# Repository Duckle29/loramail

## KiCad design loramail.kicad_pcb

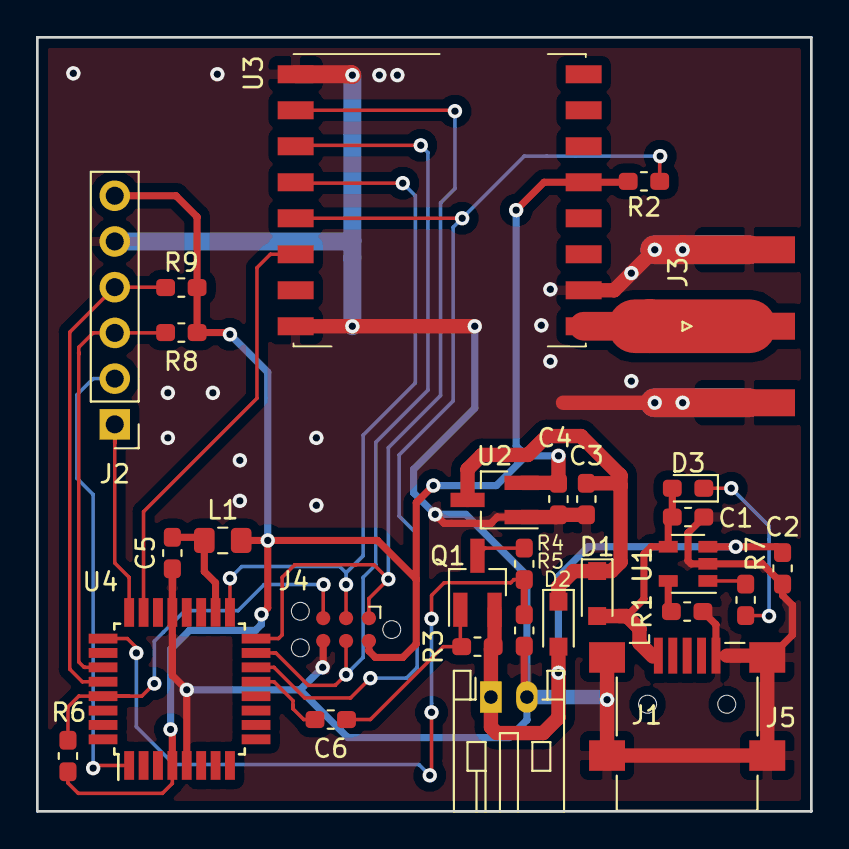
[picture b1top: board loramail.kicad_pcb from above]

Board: 2 copper layers, 43.0 x 43.0 mm, 29 parts (0 on the bottom side), 24 nets.

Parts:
C1, C2: 4.7uF; C_0603_1608Metric_Pad1.05x0.95mm_HandSolder
C3, C4: 1uF; C_0603_1608Metric_Pad1.05x0.95mm_HandSolder
C5, C6: 100nF; C_0603_1608Metric_Pad1.05x0.95mm_HandSolder
D1, D2: BAT54WS; D_SOD-323_HandSoldering
D3: red; LED_0603_1608Metric_Pad1.05x0.95mm_HandSolder
J1: lipo-cell; JST_PH_S2B-PH-K_1x02_P2.00mm_Horizontal
J2: VL53L0X; PinHeader_1x06_P2.54mm_Vertical
J3: SMA; SMA_Amphenol_132289_EdgeMount
J4: TC2030-ISP; Tag-Connect_TC2030-IDC-NL_2x03_P1.27mm_Vertical
J5: USB_B_Mini; USB_Mini-B_Lumberg_2486_01_Horizontal
L1: 10uH; L_0805_2012Metric_Pad1.15x1.40mm_HandSolder
Q1: SI2333; SOT-23_Handsoldering
R1, R7: 2k2; R_0603_1608Metric_Pad1.05x0.95mm_HandSolder
R2: 100k; R_0603_1608Metric_Pad1.05x0.95mm_HandSolder
R3, R6, R8, R9: 10k; R_0603_1608Metric_Pad1.05x0.95mm_HandSolder
R4: 1k2; R_0603_1608Metric_Pad1.05x0.95mm_HandSolder
R5: 3k3; R_0603_1608Metric_Pad1.05x0.95mm_HandSolder
U1: MCP73831-2-OT; SOT-23-5
U2: MCP1703A-3302_SOT23; SOT-23_Handsoldering
U3: RFM96W-433S2; HOPERF_RFM9XW_SMD
U4: ATmega328PB-AU; TQFP-32_7x7mm_P0.8mm

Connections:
+3V3: C4.1, J2.6, J4.2, L1.1, R2.2, R6.1, R8.1, R9.1, U2.2, U3.13, U4.4
+BATT: C2.1, D2.2, J1.1, Q1.2, R3.1, U1.3
/bat-sense: R4.2, R5.1, U4.25
/sample-bat: C6.1, U4.13
GND: C1.1, C2.2, C3.2, C4.2, C5.2, J1.2, J2.5, J3.2, J4.6, J5.5, J5.6, R1.1, R5.2, U1.2, U2.1, U3.1, U3.8, U3.10, U4.5, U4.21
MISO: J4.1, U3.2, U4.16
MOSI: J4.4, U3.3, U4.15
NSS: R2.1, U3.5, U4.14
unnamed: C3.1, D1.1, D2.1, U2.3
unnamed: C5.1, L1.2, U4.18
unnamed: C6.2, Q1.1, R3.2
unnamed: D3.1, R7.1
unnamed: J3.1, U3.9
unnamed: Q1.3, R4.1
unnamed: R1.2, U1.5
unnamed: R7.2, U1.1
RFM-RST: U3.6, U4.23
SCK: J4.3, U3.4, U4.17
SCL: J2.4, R9.2, U4.28
SDA: J2.3, R8.2, U4.27
ToF-INT: J2.2, U4.1
ToF-XSH: J2.1, U4.24
VBUS: C1.2, D1.2, D3.2, J5.1, U1.4
~RESET: J4.5, R6.2, U4.29
